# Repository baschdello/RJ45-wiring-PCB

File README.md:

# RJ45-wiring-PCB
small PCB with two RJ45 jacks and pin headers

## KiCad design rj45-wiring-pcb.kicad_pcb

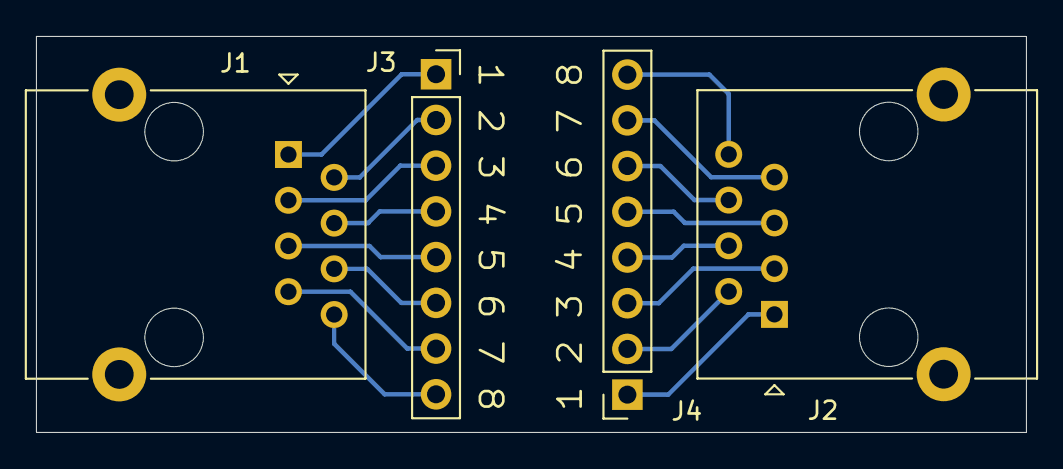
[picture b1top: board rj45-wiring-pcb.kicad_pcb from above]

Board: 2 copper layers, 55.0 x 22.0 mm, 4 parts (0 on the bottom side), 16 nets.

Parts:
J1, J2: RJ45; RJ45_Ninigi_GE
J3, J4: Conn_01x08_Female; PinSocket_1x08_P2.54mm_Vertical

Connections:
unnamed: J1.1, J3.1
unnamed: J1.2, J3.2
unnamed: J1.3, J3.3
unnamed: J1.4, J3.4
unnamed: J1.5, J3.5
unnamed: J1.6, J3.6
unnamed: J1.7, J3.7
unnamed: J1.8, J3.8
unnamed: J2.1, J4.1
unnamed: J2.2, J4.2
unnamed: J2.3, J4.3
unnamed: J2.4, J4.4
unnamed: J2.5, J4.5
unnamed: J2.6, J4.6
unnamed: J2.7, J4.7
unnamed: J2.8, J4.8

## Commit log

2022-09-25 initial
